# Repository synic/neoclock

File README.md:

# NeoClockº

A WS2812B LED-based analog clock that uses a DS3231 real-time clock module for accurate timekeeping.

## Features

- Multiple display modes for clock face
- 11 color schemes
- Brightness adjustment with 5 levels
- Battery backup with RTC
- Automatic fallback mode if RTC fails
- Diagnostic routines for troubleshooting

## Hardware Requirements

- Arduino Micro (or compatible board)
- DS3231 RTC module
- WS2812B LED strip (60 LEDs)
- 4 push buttons for control
- USB power supply

## Installation

1. Install the arduino-cli:

   ```bash
   $ brew install arduino-cli   # macOS
   ```

2. Edit `vars.mak` and update any values to match your system.

3. Plug in your board and run `make` to compile and upload.

## Usage

The clock has four buttons for control:

- HOUR: Increment hour
- MINUTE: Increment minute
- BRIGHTNESS: Cycle through brightness levels
- MODE: Cycle between setting modes

Hold HOUR + BRIGHTNESS to reset to defaults.

## Development

This project uses FastLED for LED control and RTCLib for the real-time clock. The code is structured with:
- Comprehensive hardware configuration
- Multiple display modes and color schemes
- RTC diagnostics and fallback modes

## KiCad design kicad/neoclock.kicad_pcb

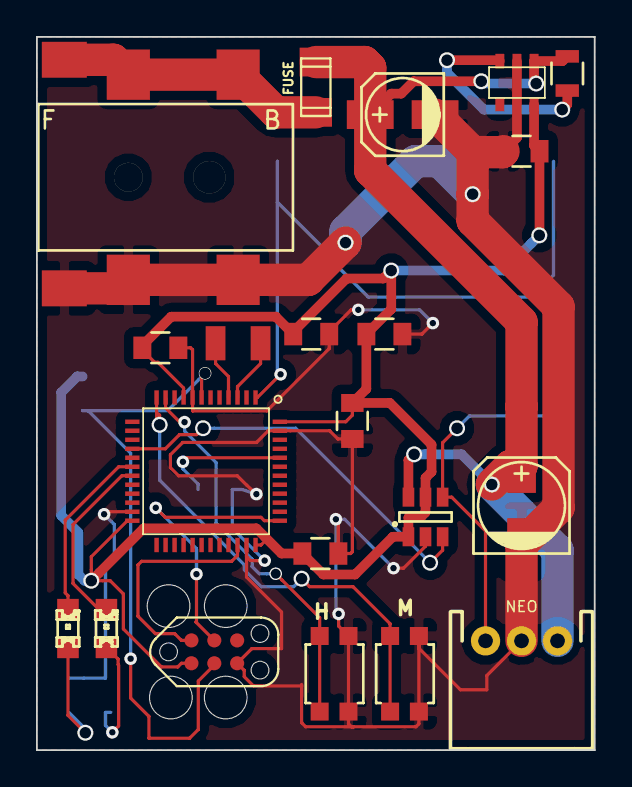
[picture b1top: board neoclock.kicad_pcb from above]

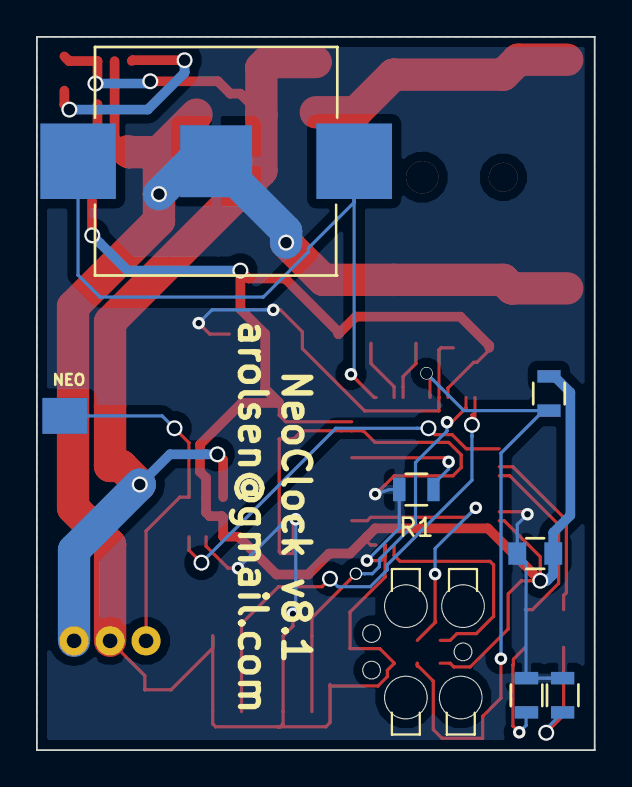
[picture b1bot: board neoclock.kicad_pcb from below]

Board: 2 copper layers, 31.0 x 39.6 mm, 30 parts (7 on the bottom side), 20 nets.

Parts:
BT1: 3v; BK-755_12mm_coincell
C1: 4.7uF; C_0805
C2, C3: 1uF; C_0805
C5, C7, C8: 100nF; C_0805
C6: 10nF; C_0805
C9: 100uF; c_elec_5x5.3
C10: 10uF; c_elec_4x4.5
CON1: 1.2mm 5v; BARREL_JACK_SMD
D1: RED; LED-0805
D2: GREEN; LED-0805
F1: FUSE; 1206_polyfuse
P1: TC2030-CTX; TC2030_SMALL
P2: NEO; jst-3-pth-ra
R1, R2, R4: 10k; R_0805
R5, R6: 330; R_0805
SW1: H; KMR2_MICROMINIATURE_BUTTON
SW2: M; KMR2_MICROMINIATURE_BUTTON
U1: stm32f303x; LQFP48
U2: TLV702xx; SOT23-5
U3: TXS0101; SOT-23-6
U4: NEO; TESTPOINT
U5: GND; TESTPOINT
U6: VCC5V; TESTPOINT
Y1: 32.768 KHz; 2_SMD_CRYSTAL_3.2x1.5

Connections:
GND: BT1.2, C1.2, C2.2, C3.2, C5.2, C6.2, C7.2, C8.2, C9.2, C10.2, CON1.2, CON1.3, P1.5, P2.2, R1.2, R5.1, R6.1, SW1.2, SW2.2, U1.8, U1.23, U1.35, U1.47, U2.2, U3.2, U5.1
NRST: P1.3, R2.1, U1.7
unnamed: BT1.1, U1.1
unnamed: CON1.1, F1.1, U6.1
unnamed: D1.1, U1.18
unnamed: D1.2, R5.2
unnamed: D2.1, U1.19
unnamed: D2.2, R6.2
unnamed: P2.3, U3.4, U4.1
unnamed: R1.1, U1.44
unnamed: R4.1, U2.3
unnamed: SW1.1, U1.11
unnamed: SW2.1, U1.12
unnamed: U1.3, Y1.1
unnamed: U1.4, Y1.2
unnamed: U1.16, U3.3
SWCLK: P1.4, U1.37
SWDIO: P1.2, U1.34
VCC5V: C9.1, C10.1, F1.2, P2.1, R4.2, U2.1, U3.6
VDD: C1.1, C2.1, C3.1, C5.1, C6.1, C7.1, C8.1, P1.1, R2.2, U1.9, U1.24, U1.36, U1.48, U2.5, U3.1, U3.5

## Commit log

2014-03-15 started repo
2014-04-03 woot
2014-04-03 reimplement map as mapRange, that supports doubles and rounding
2014-04-03 make it a bit fancier. 1 LED == hour, 2 LED == minute, 3 LED == second
2014-04-03 since it's not really a fully function linkedlist, rename it to something else that more matches it's specific use.
2014-04-03 ifdef needs updating
2014-04-04 it works
2014-04-04 works some more
2014-04-04 color blending woo
2014-04-04 I can spll
2014-04-04 better
2014-04-07 done
2014-04-08 yeah
2014-04-08 awh yeah
2014-04-09 added pcb start
2014-04-26 for 60 LED ring
2014-04-28 updating clock board
2014-04-29 jst, bitches
2014-05-16 add autobrightness support
2014-05-16 whoops, I actually *don't* want the inverse.
2014-06-03 updating pcb finally
2014-06-23 dammit
2014-06-27 updated to the new smaller, attiny84 based board
2014-06-28 bleh
2014-06-28 hour and minute buttons work
2014-06-28 actually show the minutes :)
2014-06-29 tweaked the colors a bit
2014-06-30 trying to fix hour display
2014-06-30 more updates
2014-07-02 holy crap fixed
2014-07-02 reenable the good stuff
2014-07-02 hour and minutes buttons totally work now
2014-07-03 label sucks
2014-07-14 updated qfn board
2014-07-14 commit latest changes for orsonz
2014-07-15 add ftdi headers
2014-07-15 add updated sketch
2014-07-15 saving
2014-07-15 all routed
2014-07-21 stuff
2014-07-21 updated pcb
2014-07-23 ditch RoundClock. It was idiotic.
2014-07-24 59, not 60
2014-07-25 changed stuff
2014-07-29 updates to the new board
2014-07-30 new board has lots of changes
2014-08-08 lots of code updates
2014-09-22 sweet
2014-09-22 schematic is mostly done
2014-09-24 started to get somewhere here
2014-10-01 board is done?
2014-10-01 organized, got ready for stm32f3
2014-10-02 formatting and such
2014-10-02 trying to align the dma_buffer and it's struct
2014-10-02 move back
2014-10-04 it's starting to work!
2014-10-04 better startup file
2014-10-04 almost done
2014-10-06 wooters
2014-10-26 fixed the board
2015-01-21 fixing up
2015-05-17 updating
2015-05-18 updating board
2015-10-04 dos -> unix. Not sure how this happened
    Bunch of the files had dos line endings, and I'm not sure why.
    Also updated to work on OS X with the latest stm32periphlib
2025-05-16 chore: upload norry's sketch
2025-05-16 save max brightness
2025-05-17 feat: brighten up default colorscheme
2025-05-17 fix: fix animation again
2025-05-17 fix: diagnostics on outliers
2025-05-17 fix: init i2c
2025-05-17 chore: move i2c
2025-05-18 chore: more rtf diagnostics
2025-05-18 fix: some animation stuff
2025-05-18 feat: use FastLED
2025-05-19 fix: fix rtc init
2025-05-21 chore: improve project structure and documentation
    - Improve constant naming and organization
    - Add button index enum for better readability
    - Update requirements.txt to match actual dependencies
    - Enhance README with better documentation
    - Add arduino-manifest tools for dependency tracking
    - Create automatic manifest generation
2025-05-24 chore: change to metro
2025-06-11 misc: updates
